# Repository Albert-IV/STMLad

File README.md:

# The STMLad keyboard

This is a 34-36 key keyboard with an on-board MCU.  Based off of the Draculad.

## State of the project
- Everything is WIP

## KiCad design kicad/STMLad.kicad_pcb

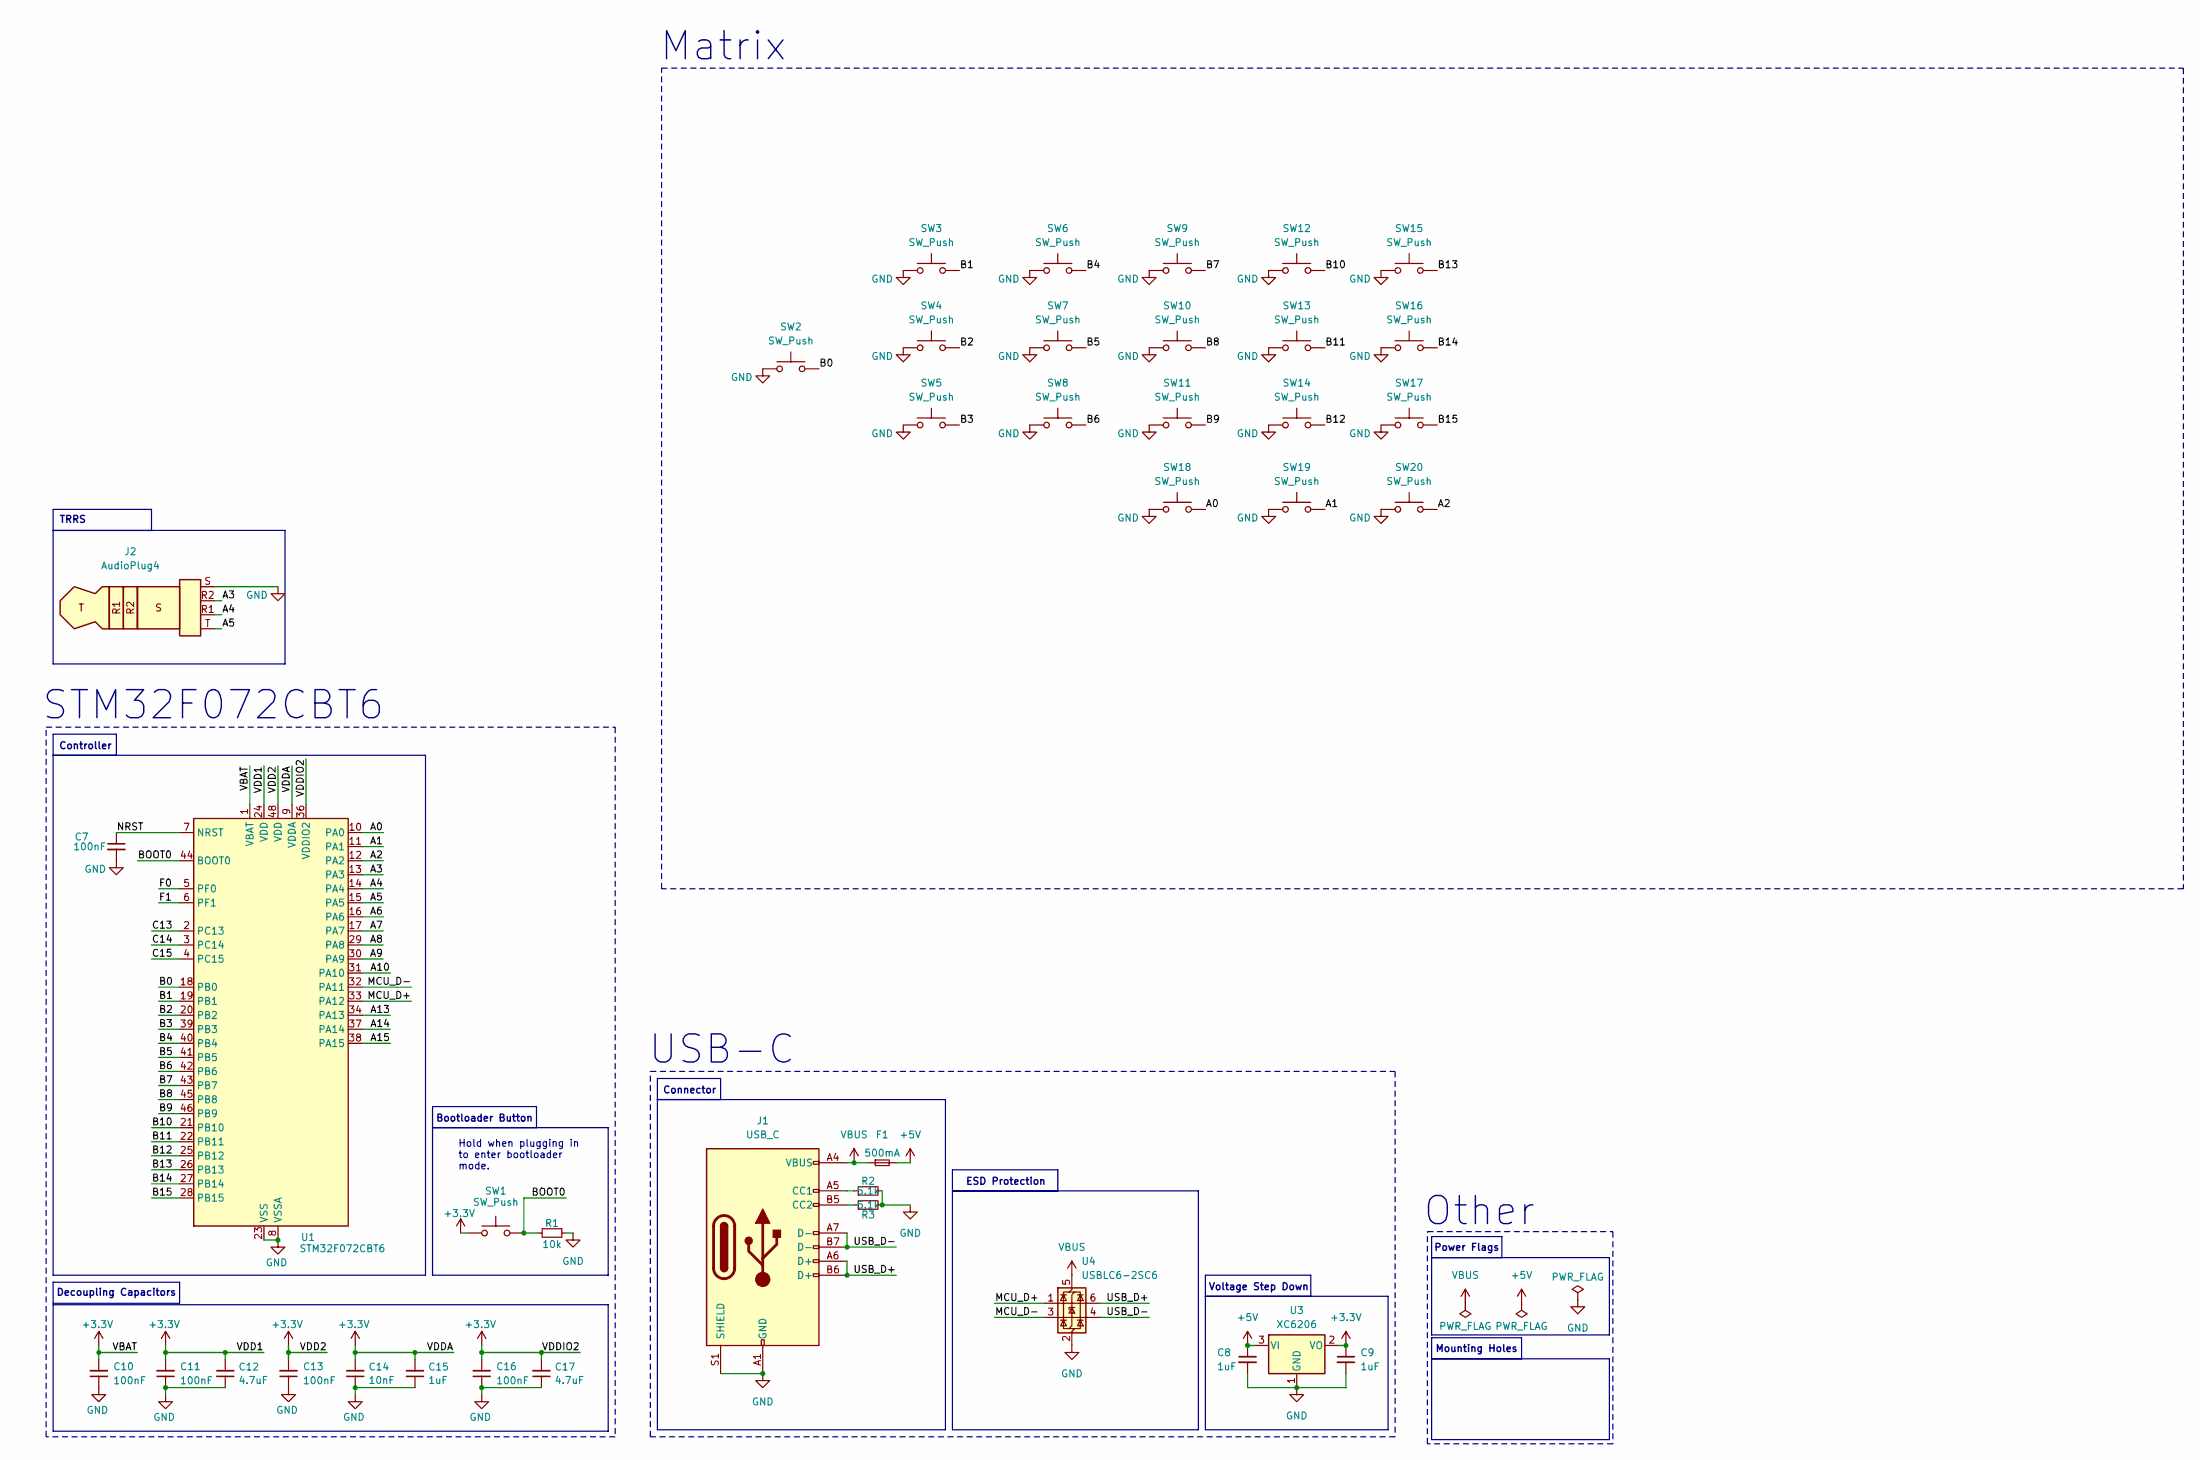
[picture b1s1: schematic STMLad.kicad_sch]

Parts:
C7: 100nF; Capacitor_0402; LCSC C307331
C8, C9: 1uF; Capacitor_0402; LCSC C52923
C10, C11, C13, C16: 100nF; Capacitor_0402; MPN CL05B104KB54PNC; LCSC C307331
C12, C17: 4.7uF; Capacitor_0402; MPN CL05A475MP5NRNC; LCSC C23733
C14: 10nF; Capacitor_0402; MPN CL05B103KB5NNNC; LCSC C15195
C15: 1uF; Capacitor_0402; MPN CL05A105KA5NQNC; LCSC C52923
F1: 500mA; Fuse_0603; LCSC C210357
J1: USB_C; USB_C_HRO_TYPE-C-31-M-12; LCSC C165948
J2: AudioPlug4
R1: 10k; Resistor_0402; LCSC C25744
R2, R3: 5.1k; Resistor_0402; LCSC C25905
SW1: SW_Push; Button_TL3342; LCSC C115351
SW2, SW3, SW4, SW5, SW6, SW7, SW8, SW9, SW10, SW11, SW12, SW13, SW14, SW15, SW16, SW17, SW18, SW19, SW20: SW_Push; SW_MX_reversible
U1: STM32F072CBT6; Package_LQFP-48_7x7mm_P0.5; LCSC C81720
U3: XC6206; Voltage_SOT-23; LCSC C5446
U4: USBLC6-2SC6; ESD_SOT-23-6; LCSC C2827654

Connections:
+3.3V: C9.1, C10.2, C11.2, C12.2, C13.2, C14.2, C15.2, C16.2, C17.2, SW1.1, U1.1 (VBAT), U1.9 (VDDA), U1.24 (VDD), U1.36 (VDDIO2), U1.48 (VDD), U3.2 (VO)
+5V: C8.1, F1.2, U3.3 (VI)
/A0: SW18.2, U1.10 (PA0)
/A1: SW19.2, U1.11 (PA1)
/A2: SW20.2, U1.12 (PA2)
/A3: J2.R2, U1.13 (PA3)
/A4: J2.R1, U1.14 (PA4)
/A5: J2.T, U1.15 (PA5)
/A6: U1.16 (PA6)
/A7: U1.17 (PA7)
/A8: U1.29 (PA8)
/A9: U1.30 (PA9)
/A10: U1.31 (PA10)
/A13: U1.34 (PA13)
/A14: U1.37 (PA14)
/A15: U1.38 (PA15)
/B0: SW2.2, U1.18 (PB0)
/B1: SW3.2, U1.19 (PB1)
/B2: SW4.2, U1.20 (PB2)
/B3: SW5.2, U1.39 (PB3)
/B4: SW6.2, U1.40 (PB4)
/B5: SW7.2, U1.41 (PB5)
/B6: SW8.2, U1.42 (PB6)
/B7: SW9.2, U1.43 (PB7)
/B8: SW10.2, U1.45 (PB8)
/B9: SW11.2, U1.46 (PB9)
/B10: SW12.2, U1.21 (PB10)
/B11: SW13.2, U1.22 (PB11)
/B12: SW14.2, U1.25 (PB12)
/B13: SW15.2, U1.26 (PB13)
/B14: SW16.2, U1.27 (PB14)
/B15: SW17.2, U1.28 (PB15)
/BOOT0: R1.2, SW1.2, U1.44 (BOOT0)
/C13: U1.2 (PC13)
/C14: U1.3 (PC14)
/C15: U1.4 (PC15)
/F0: U1.5 (PF0)
/F1: U1.6 (PF1)
/MCU_D+: U1.33 (PA12), U4.1 (I/O1)
/MCU_D-: U1.32 (PA11), U4.3 (I/O2)
/NRST: C7.1, U1.7 (NRST)
/USB_D+: J1.A6 (D+), J1.B6 (D+), U4.6 (I/O1)
/USB_D-: J1.A7 (D-), J1.B7 (D-), U4.4 (I/O2)
GND: C7.2, C8.2, C9.2, C10.1, C11.1, C12.1, C13.1, C14.1, C15.1, C16.1, C17.1, J1.A1 (GND), J1.A12 (GND), J1.B1 (GND), J1.B12 (GND), J1.S1 (SHIELD), J2.S, R1.1, R2.2, R3.2, SW2.1, SW3.1, SW4.1, SW5.1, SW6.1, SW7.1, SW8.1, SW9.1, SW10.1, SW11.1, SW12.1, SW13.1, SW14.1, SW15.1, SW16.1, SW17.1, SW18.1, SW19.1, SW20.1, U1.8 (VSSA), U1.23 (VSS), U1.35 (VSS), U1.47 (VSS), U3.1 (GND), U4.2 (GND)
unnamed: J1.A5 (CC1), R2.1
unnamed: J1.B5 (CC2), R3.1
VBUS: F1.1, J1.A4 (VBUS), J1.A9 (VBUS), J1.B4 (VBUS), J1.B9 (VBUS), U4.5 (VBUS)

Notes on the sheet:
TRRS
Hold when plugging in to enter bootloader mode.
STM32F072CBT6
USB-C
Mounting Holes
Decoupling Capacitors
Controller
ESD Protection
Power Flags
Voltage Step Down
Other
Bootloader Button
Matrix
Connector

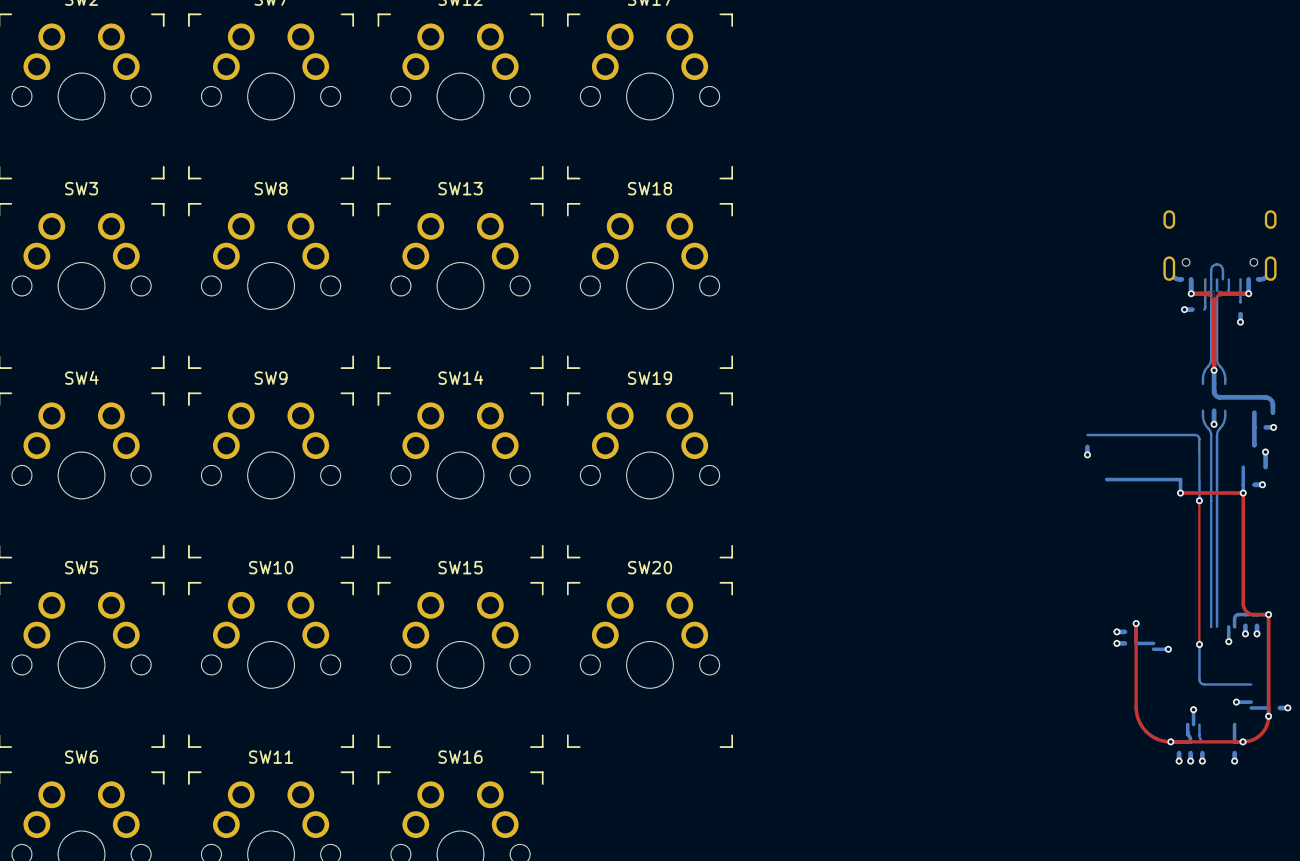
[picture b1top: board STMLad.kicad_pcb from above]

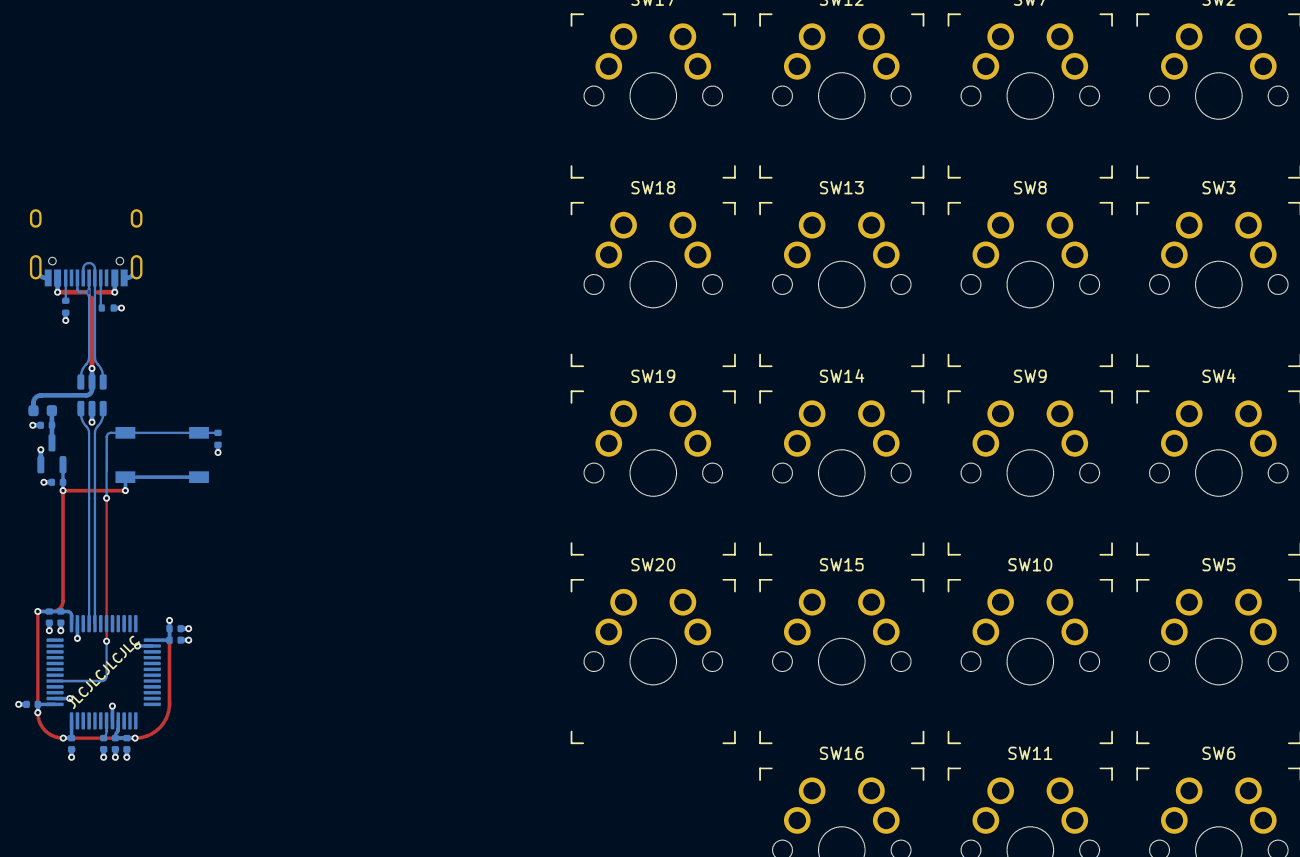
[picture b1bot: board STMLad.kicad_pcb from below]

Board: 4 copper layers, 39 parts (20 on the bottom side), 31 nets.

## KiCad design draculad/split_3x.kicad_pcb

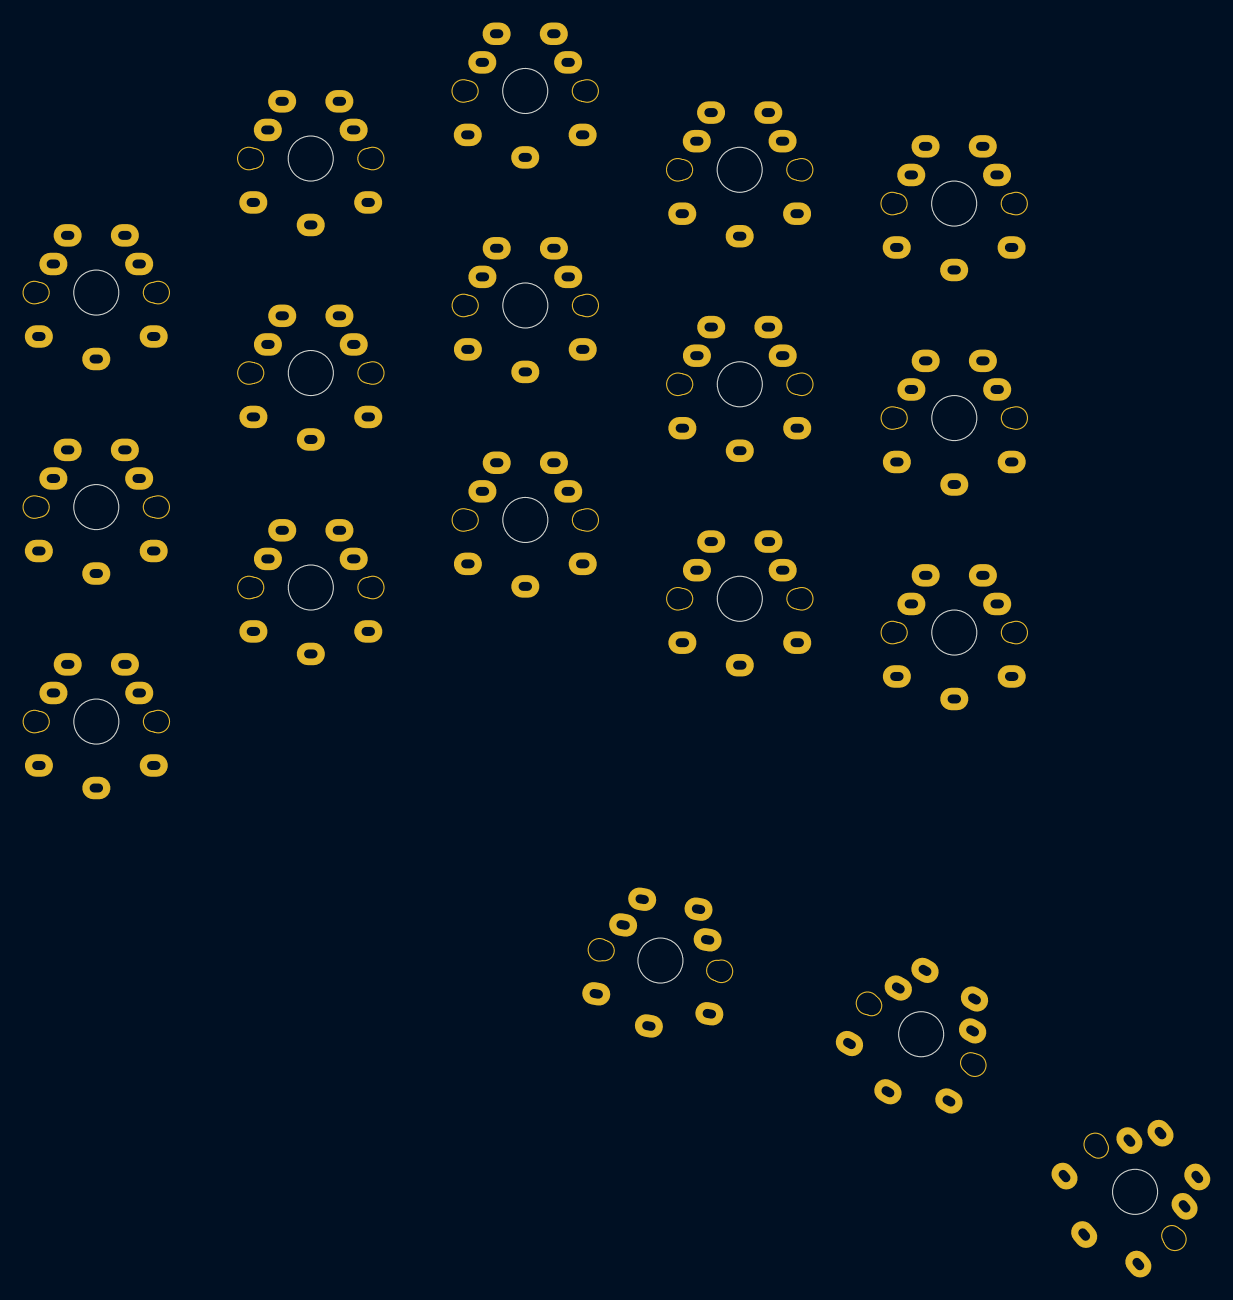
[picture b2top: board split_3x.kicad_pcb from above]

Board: 2 copper layers, 18 parts (0 on the bottom side), 5 nets, no tracks yet.

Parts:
MX1, MX2, MX3, MX4, MX5, MX6, MX7, MX8, MX9, MX10, MX11, MX12, MX13, MX14, MX15, MX16, MX17, MX18: MX-NoLED; CherryMX_Choc_1u_reversible

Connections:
col0: MX1.1, MX2.1, MX3.1
col1: MX4.1, MX5.1, MX6.1
col2: MX7.1, MX8.1, MX9.1, MX10.1
col3: MX11.1, MX12.1, MX13.1, MX14.1
col4: MX15.1, MX16.1, MX17.1, MX18.1

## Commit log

2024-07-24 Remove Draculad-specific files
2024-07-25 Set up initial schematic
